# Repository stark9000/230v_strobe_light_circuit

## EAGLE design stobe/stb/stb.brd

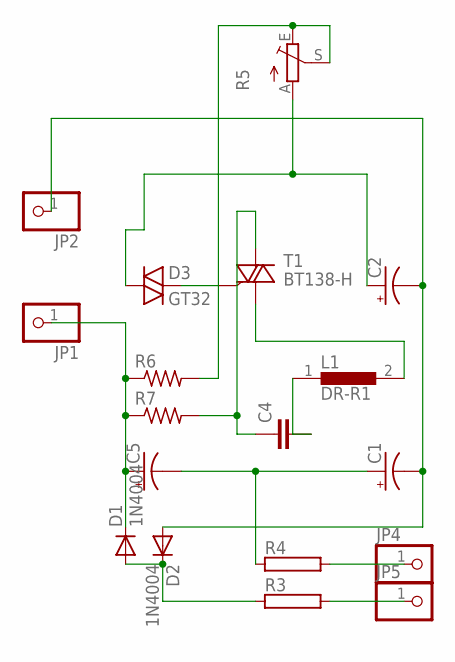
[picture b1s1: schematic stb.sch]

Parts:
C1, C2, C5: CPOL-USE7.5-16; E7,5-16
C4: C10/5; C10B5
D1, D2: 1N4004; DO41-10
D3: GT32
JP1, JP2, JP4, JP5: PINHD-1X1; 1X01
L1: DR-R1
R3, R4: RKWP336; KWP336
R5: TRIM_EU-LI10; LI10
R6, R7: R-US_0207/7; 0207/7
T1: BT138-H; TO220BH

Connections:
unnamed: JP4.1, R4.2
unnamed: C5.+, D1.C, JP1.1, R6.1, R7.1
unnamed: D1.A, D2.C, R3.1
unnamed: JP5.1, R3.2
unnamed: C1.+, C5.-, R4.1
unnamed: C1.-, C2.-, D2.A, JP2.1
unnamed: D3.2, T1.G
unnamed: C4.1, R7.2, T1.T2 (A2)
unnamed: L1.2, T1.T1 (A1)
unnamed: C4.2, L1.1
unnamed: C2.+, D3.1, R5.A
unnamed: R5.E, R5.S, R6.2

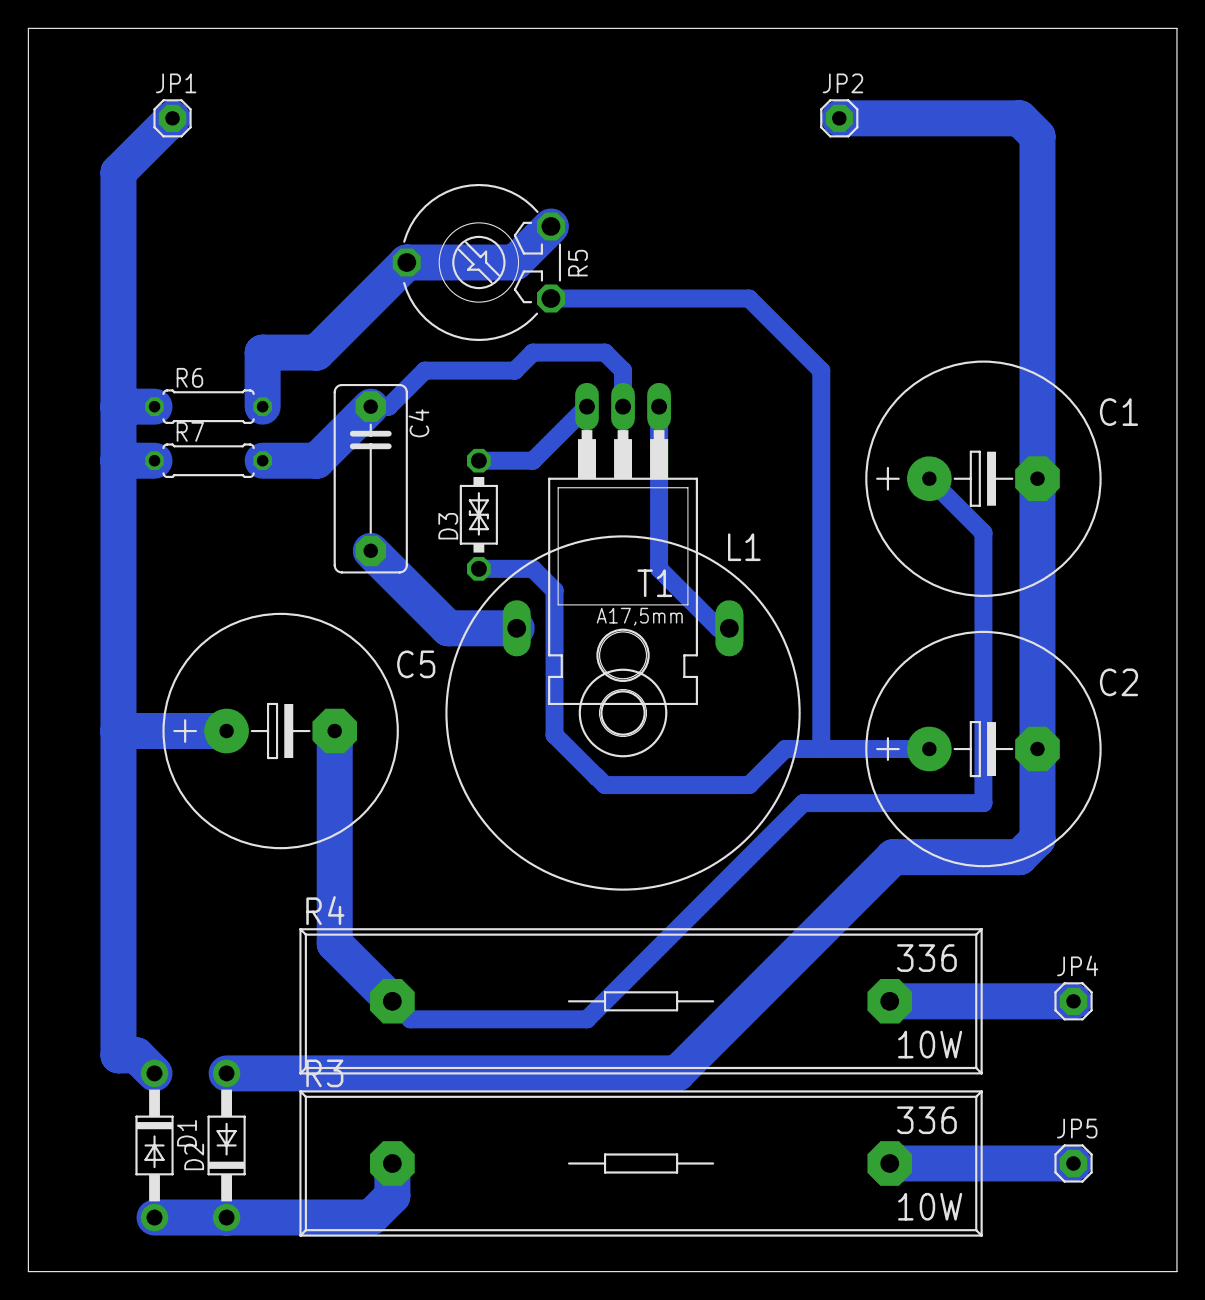
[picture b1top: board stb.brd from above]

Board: 2 copper layers, 81.0 x 87.6 mm, 18 parts (0 on the bottom side), 12 nets.
